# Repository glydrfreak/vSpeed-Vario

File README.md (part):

### This repository contains all previous prototypes. </br>
### Click <a href="https://github.com/glydrfreak/vSpeedVario-mini">here</a> for the final product repository. </br>
<table float="center">
  <tr>
    <td align="center" width=50%>
      <h1>v^Speed Vario</h1>
      Contents:</br>
      <a href="https://github.com/glydrfreak/vSpeedVario-mini">v^SPEED VARIO mini</a></br>
      <a href="#compare">Compare</a> </br>
      <a href="#vspeed-vario">Android App</a></br>
      <a href="#flyskyhy">iPhone App</a> </br>
      <a href="#solidworks">3D Printing</a> </br>
      <a href="#arduino-ide">Arduino Code</a> </br>
      <a href="#eagle-cad">Custom Circuit Board</a> </br>
      <a href="#bill-of-materials">Parts List</a> </br>
    </td>
    <td align="center"> 
      <h3>DIY Paragliding Variometer</h3>
       
      <h6>(Vertical Speed Indicator)</h6>
    </td>
  </tr>
</table>

<table>
  <tr>
    <td width=33% vAlign="top" align="center">
      <h2>v^SPEED VARIO mini</h2>
      <h3>$99</h3>
       </br>
         Email vSpeedVario@gmail.com to purchase </br>
      <a href="#vspeed-vario">Back to Top</a> </br>
    </td>
    <td width=66%> 
      <ul>
        <h3>SPECS:</h3>
        <li>Ultra-high precision barometric pressure sensor detects altitude changes as small as 10cm</li>
        <li>Lowest priced Bluetooth Variometer on the market</li>
        <li>iPhone users: Fully compatible with <a href="#flyskyhy">FlySkyHy</a> app</li>
        <li>Android users: <a href="#vspeed">v^SPEED</a> app new in Google Play Store</li>
        <li>Fully compatiple with Arduino IDE to easily change custom settings</li>
        <li>Mounts on risers with velcro</li>
        (leash, and velcro for both riser and vario included)
        <li>Tiny Size: 68x25x10mm (about the size of a man's thumb)</li>
        <li>3D printed cover screws onto circuit board </li>
          (black, white, yellow, or light blue)
        <li>Power switch, and volume buttons</li>
        <li>100mAh lipo battery with microUSB charging port</li>
        <li>7hr battery life while streaming bluetooth data</li>
        <li>1hr charging time</li>
        <li>Sale price: $99 each (subject to change)</li>
        <h3>OR -- DIY! --</h3><h6>(assuming you have a 3D printer, an SWD programmer, and a reflow oven)</h6>
        <li>1 hand assembled: ~ $70 each </li>
        <li>10 hand assembled: ~ $38 each</li>
        <li>10 machine assembled: ~ $89 each</li>
        <li>100 machine assembled: ~ $59 each</li>
      </ul>
    </td>
  </tr>
</table>

<table>
  <tr>
    <td width=33% vAlign="top" align="center">
      <h2>v^SPEED Vario</h2>
      
      <a href="#vspeed-vario">Back to Top</a> </br>
    </td>
    <td width="66%"> 
      <ul>
        <h3>Android App--</h3>
        I have modified Adafruit's "Bluefruit LE Connect" for Android and the source code can be found in the Android folder. Now published to Google Play! </br>
  </br>
        This app will give you a better image of what your v^SPEED Vario is doing as it transmits live bluetooth data of barometric altitude, vertical speed, and battery level. Other features include implemented GPS for GPS altitude, ground speed, and heading. The implemented Audio beeps are helpful for listening to each foot of climb as well as a variable sink tone. An implemented accelerometer is for keeping track of max G-force during a hard turn or spiral. The visual display includes a line chart of vertical speed, as well as scrolling altitude numbers so you can see your precise vertical velocity. The climb and sink thresholds are adjustable within the app, which also change the thresholds on the external vario automatically.
      </ul>
    </td>
  </tr>
</table>

<table>
  <tr>
    <td width=33% vAlign="top" align="center">
      <h2>Flyskyhy</h2>
      
      <a href="#vspeed-vario">Back to Top</a> </br>
    </td>
    <td width=66%> 
      <ul>
        <h3>iOS App by Renevision--</h3>
        I've been working with Rene to get v^SPEED VARIO compatible with the World's most popular Paragliding app! He's been very helpful throughout the process, and Flyskyhy is an unbeatable iPhone application when it comes to flying. v^Speed Vario is currently using the same protocol as SkyDrop variometers, so in the app when selecting your device, you must choose SkyDrop for the time being.  
      </ul>
    </td>
  </tr>
</table>

<h1>Prior Prototypes:</h1>

<table>
  <tr>
    <td width=33% vAlign="top" align="center">
      <h2>PROTOTYPE5</h2>
      <h4>(In Progress)</h4>
      
      <a href="#vspeed-vario">Back to Top</a> </br>
    </td>
    <td width=66%> 
      <ul>
        <h3>IMPROVEMENTS:</h3>
        <li>Nokia 5110 LCD is much cheaper</li>
        <li>2.9" e-Paper display was having interference issues</li>
        <li>Three buttons used for interfacing with menu</li>
        <li>Screw-together 3D printed case is much more printer friendly</li>
        <li>Size: 97x47x18mm</li>
        <li>Material cost for ten: ~ $54 each</li>
        <li>Material cost for one: ~ $96 each</li>
      </ul>
    </td>
  </tr>
</table>

<table>
  <tr>
    <td width=33% vAlign="top" align="center">
      <h2>PROTOTYPE4</h2>
      <h4>(Aborted)</h4>
      
      <a href="#vspeed-vario">Back to Top</a> </br>
    </td>
    <td width=66%> 
      <ul>
        <h3>IMPROVEMENTS:</h3>
        <li>Bluetooth compatible with:</li>
        <ul>
          <li>iPhone: Flyskyhy</li>
          <li>Android: v^Speed (soon to be published)</li>
        </ul>
        <li>2.9" e-Paper display is much larger</li>
        <li>Amplified electromagnetic buzzer is much louder</li>
        <li>Micro SD saves settings and any desired flight data</li>
        <li>Single Button power-on also used for interfacing with menu</li>
        <li>Machine assembly potential: All SMD components, except the switch</li>
        <li>Size: 100x40x30mm</li>
        <li>Material cost for ten: $69 each</li>
        <li>Material cost for one: $111 each</li>
      </ul>
    </td>
  </tr>
</table>

<table>
  <tr>
    <td width=33% align="center" vAlign="top">
      <h2>PROTOTYPE3</h2>
      <h4>(Fully Working)</h4>
       
      <a href="#vspeed-vario">Back to Top</a> </br>
    </td>
    <td width=66%> 
      <ul>
        <h3>IMPROVEMENTS:</h3>
        <li>Bluetooth compatible with:</li>
        <ul>
          <li>iPhone: Flyskyhy</li>
          <li>Android: v^SPEED (soon to be published)</li>
        </ul>
        <li>Adafruit Feather Bluefruit M0</li>
        <li>MS5611 Barometric Pressure/Temperature Sensor (SPI mode) </li>
        <li>Less than several INCHES of altitude noise with a simple averaging filter</li>
        <li>37 Altitude samples per second with the display screen ON</li>
        <li>56 Altitude samples per second while connected to your phone with the display screen OFF</li>
        <li>Size: 60x28x20mm (perfect for wrist watch, or riser mounting)</li>
        <li>0.66" OLED display (SPI mode)</li>
        <li>PS1740 Piezo Buzzer</li>
        <li>3D Printed Case</li>
        <li>Custom designed PCB</li>
        <li>Audio and a handful of widgets are implemented in each app</li>
        <li>Material cost for ten: $45 each</li>
        <li>Material cost for one: $77 each</li>
      </ul>
    </td>
  </tr>
</table>

<table>
  <tr>
    <td width=33% align="center" vAlign="top">
      <h2>PROTOTYPE2</h2>
      <h4>(Discontinued)</h4>
       
      <a href="#vspeed-vario">Back to Top</a> </br>
    </td>
    <td width=66%> 
      <ul>
        <h3>IMPROVEMENTS:</h3>
        <li>Bluetooth compatible with:</li>
        <ul>
          <li>iPhone: (Not yet compatible) </li>
          <li>Android: v^SPEED (soon to be published)</li>
        </ul>
        <li>Adafruit Feather Bluefruit 32u4</li>
        <li>MS5611 Barometric Pressure/Temperature Sensor (SPI mode) </li>
        <li>Less than several INCHES of altitude noise with a simple averaging filter</li>
        <li>21 Altitude samples per second with the display screen ON</li>
        <li>49 Altitude samples per second while connected to your phone with the display screen OFF</li>
        <li>Size: 60x20x28mm (perfect for wrist watch, or riser mounting)</li>
        <li>0.66" OLED display (SPI mode)</li>
        <li>PS1740 Piezo Buzzer</li>
        <li>3D Printed Case</li>
        <li>Custom designed PCB</li>
        <li>Audio and a handful of widgets are implemented in the  v^SPEED app</li>
        <li>Material cost for ten: $45 each</li>
        <li>Material cost for one: $77 each</li>
      </ul>
    </td>
  </tr>
</table>

<table>
  <tr>
    <td width=33% align="center" vAlign="top">
      <h2>PROTOTYPE1</h2>
      <h4>(One of a kind)</h4>
      
      <a href="#vspeed-vario">Back to Top</a> </br>
    </td>
    <td width=66%> 
      <ul>
        <h3>SPECIFICATIONS:</h3>
        <li>Arduino Nano</li>
        <li>BMP180 Barometric Pressure/Temperature Sensor (I2C mode)</li>
        <li>Just about a foot of altitude noise with a simple averaging filter</li>
        <li>13 Altitude samples per second</li>
        <li>Size: 60x20x28mm (perfect for wrist watch, or riser mounting)</li>
        <li>NOKIA5110 LCD Display (SPI mode)</li>
        <li>Backlight Control</li>
        <li>Volume Control</li>
        <li>PS1240 Piezo Buzzer</li>
        <li>Material cost for one: $20</li>
      </ul>
    </td>
  </tr>
</table>

<table border="1" align="center" >
  <tr> 
    <td VAlign="bottom"> 
      <h3>COMPARE:</h3><br/>
      <a href="#vspeed-vario">Back to Top</a> </br>
       
    </td>
    <td width="20%" align="center"> 	</td>
    <td width="20%" align="center"> 	</td>	
    <td width="20%" align="center"> 	</td>
    <td width="20%" align="center"> 	</td>
    <td width="20%" align="center"> 	</td>
    <td width="20%" align="center"> 	</td>
  </tr>
  <tr> 
    <td align="center"> <b>Model</b> </td>
    <td align="center"> <b>PROTOTYPE1</b>	</td>
    <td align="center"> <b>PROTOTYPE2</b>	</td>	
    <td align="center"> <b>PROTOTYPE3</b>	</td>
    <td align="center"> <b>PROTOTYPE4</b>	</td>
    <td align="center"> <b>PROTOTYPE5</b>	</td>
    <td align="center"> <b>PROTOTYPE6</b>	</td>
  </tr>
  <tr> 
    <td align="center"> <b>Height x Width x Thickness (mm)</b>	 </td>
    <td align="center"> 100 x 70 x 20		</td>
    <td align="center"> 	60 x 28 x 20	</td>	
    <td align="center">  60 x 28 x 20	</td>
    <td align="center"> 100 x 40 x 30	</td>
    <td align="center"> 97 x 47 x 18	</td>
    <td align="center"> 68 x 25 x 10	</td>
  </tr>
  <tr> 
    <td align="center"> <b>Controller</b>	 </td>
    <td align="center"> Arduino Nano		</td>
    <td align="center"> Bluefruit Feather 32u4	</td>	
    <td align="center"> Bluefruit Feather M0	</td>
    <td align="center"> Bluefruit Feather M0	</td>
    <td align="center"> Bluefruit Feather M0	</td>
    <td align="center"> ATSAMD21G18A-MU	</td>
  </tr>
  <tr> 
    <td align="center"> <b>Barometer</b>	 </td>
    <td align="center"> BMP180		</td>
    <td align="center"> MS5611	</td>	
    <td align="center"> MS5611	</td>
    <td align="center"> MS5611	</td>
    <td align="center"> MS5611	</td>
    <td align="center"> MS5611	</td>
  </tr>
  <tr> 
    <td align="center"> <b>Altitude Sample Rate (Hz)</b>	 </td>
    <td align="center"> 13		</td>
    <td align="center"> 21-49	</td>	
    <td align="center"> 37-56	</td>
    <td align="center"> (Not Tested Yet)	</td>
    <td align="center"> ~ 60 </td>
    <td align="center"> ~ 80 </td>
  </tr>  
  <tr> 
    <td align="center"> <b>Altitude Precision (cm)</b> </td>
    <td align="center"> 35		</td>
    <td align="center"> 11	</td>	
    <td align="center"> 10	</td>
    <td align="center"> (Not Tested Yet)	</td>
    <td align="center"> 10	</td>
    <td align="center"> ~ 8	</td>
  </tr>  
  <tr> 
    <td align="center"> <b>Android App Compatibility</b> </td>
    <td align="center"> -		</td>
    <td align="center"> v^SPEED	</td>	
    <td align="center"> v^SPEED	</td>
    <td align="center"> v^SPEED	</td>
    <td align="center"> v^SPEED	</td>
    <td align="center"> v^SPEED	</td>
  </tr> 
  <tr> 
    <td align="center"> <b>iPhone App Compatibility</b> </td>
    <td align="center"> - </td>
    <td align="center"> -	</td>	
    <td align="center"> Flyskyhy	</td>
    <td align="center"> Flyskyhy	</td>
    <td align="center"> Flyskyhy	</td>
    <td align="center"> Flyskyhy	</td>
  </tr> 
  <tr> 
    <td align="center"> <b>Battery</b> </td>
    <td align="center"> 9V </td>
    <td align="center"> BTG 150 mAh Li-Po 3.7V	</td>	
    <td align="center"> BTG 150 mAh Li-Po 3.7V	</td>
    <td align="center"> BTG 150 mAh Li-Po 3.7V	</td>
    <td align="center"> BTG 150 mAh Li-Po 3.7V	</td>
    <td align="center"> Adafruit 100 mAh Li-Po 3.7V	</td>
  </tr> 
  <tr> 
    <td align="center"> <b>Battery Life w/ Full Function</b> </td>
    <td align="center"> (Hasn't Died Yet) </td>
    <td align="center"> (Approx 8 hr)	</td>	
    <td align="center"> (Approx 8 hr)	</td>
    <td align="center"> (Not Tested Yet)	</td>
    <td align="center"> (Not Tested Yet)	</td>
    <td align="center"> (Not Tested Yet)	</td>
  </tr> 
  <tr> 
    <td align="center"> <b>Buzzer</b> </td>
    <td align="center"> PS1240 </td>
    <td align="center"> PS1740	</td>	
    <td align="center"> PS1740	</td>
    <td align="center"> BOT-03D-BUJEON	</td>
    <td align="center"> BOT-03D-BUJEON	</td>
    <td align="center"> SMT-1127-S-R	</td>
  </tr> 
  <tr> 
    <td align="center"> <b>Amplification</b> </td>
    <td align="center"> - </td>
    <td align="center"> - </td>	
    <td align="center"> -	</td>
    <td align="center"> Yes	</td>
    <td align="center"> Yes	</td>
    <td align="center"> Yes	</td>
  </tr> 
  <tr> 
    <td align="center"> <b>Volume Control</b> </td>
    <td align="center"> Thumbwheel </td>
    <td align="center"> Thumbwheel	</td>	
    <td align="center"> Thumbwheel	</td>
    <td align="center"> Digital	</td>
    <td align="center"> Digital	</td>
    <td align="center"> Digital	</td>
  </tr> 
  <tr> 
    <td align="center"> <b>Display</b> </td>
    <td align="center"> Nokia5110 LCD </td>
    <td align="center"> 0.66" OLED	</td>	
    <td align="center"> 0.66" OLED	</td>
    <td align="center"> 2.9" e-Paper	</td>
    <td align="center"> Nokia5110 LCD </td>
    <td align="center"> (Use Bluetooth) </td>
  </tr> 
  <tr> 
    <td align="center"> <b>Micro SD Slot</b> </td>
    <td align="center"> - </td>
    <td align="center"> -	</td>	
    <td align="center"> -	</td>
    <td align="center"> Yes	</td>
    <td align="center"> Yes	</td>
    <td align="center"> -	</td>
  </tr> 
  <tr> 
    <td align="center"> <b>User Control</b> </td>
    <td align="center"> Volume, Brightness, Power </td>
    <td align="center"> Volume, Power	</td>	
    <td align="center"> Volume, Power	</td>
    <td align="center"> Single Button	</td>
    <td align="center"> Three Button, Power	</td>
    <td align="center"> Two Button, Power	</td>
  </tr> 
  <tr> 
    <td align="center"> <b>Custom Settings</b> </td>
    <td align="center"> Arduino Upload </td>
    <td align="center"> Arduino Upload </td>	
    <td align="center"> Arduino Upload </td>
    <td align="center"> Settings Menu	</td>
    <td align="center"> Settings Menu	</td>
    <td align="center"> Arduino Upload </td>
  </tr> 
  <tr> 
    <td align="center"> <b>Mounting</b> </td>
    <td align="center"> Leg Strap </td>
    <td align="center"> Riser, Wrist	</td>	
    <td align="center"> Riser, Wrist	</td>
    <td align="center"> Riser	</td>
    <td align="center"> Leg Strap </td>
    <td align="center"> Leg Strap, Riser </td>
  </tr> 
  <tr> 
    <td align="center"> <b>Assembly</b> </td>
    <td align="center"> Cardboard, Protoboard, Wire </td>
    <td align="center"> Custom PCB Through-hole </td>    
    <td align="center"> Custom PCB Through-hole </td>
    <td align="center"> Custom PCB Surface Mount </td>  
    <td align="center"> Custom PCB Surface Mount </td>  
    <td align="center"> 100% machine assembly potential </td>  
  </tr> 
  <tr> 
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
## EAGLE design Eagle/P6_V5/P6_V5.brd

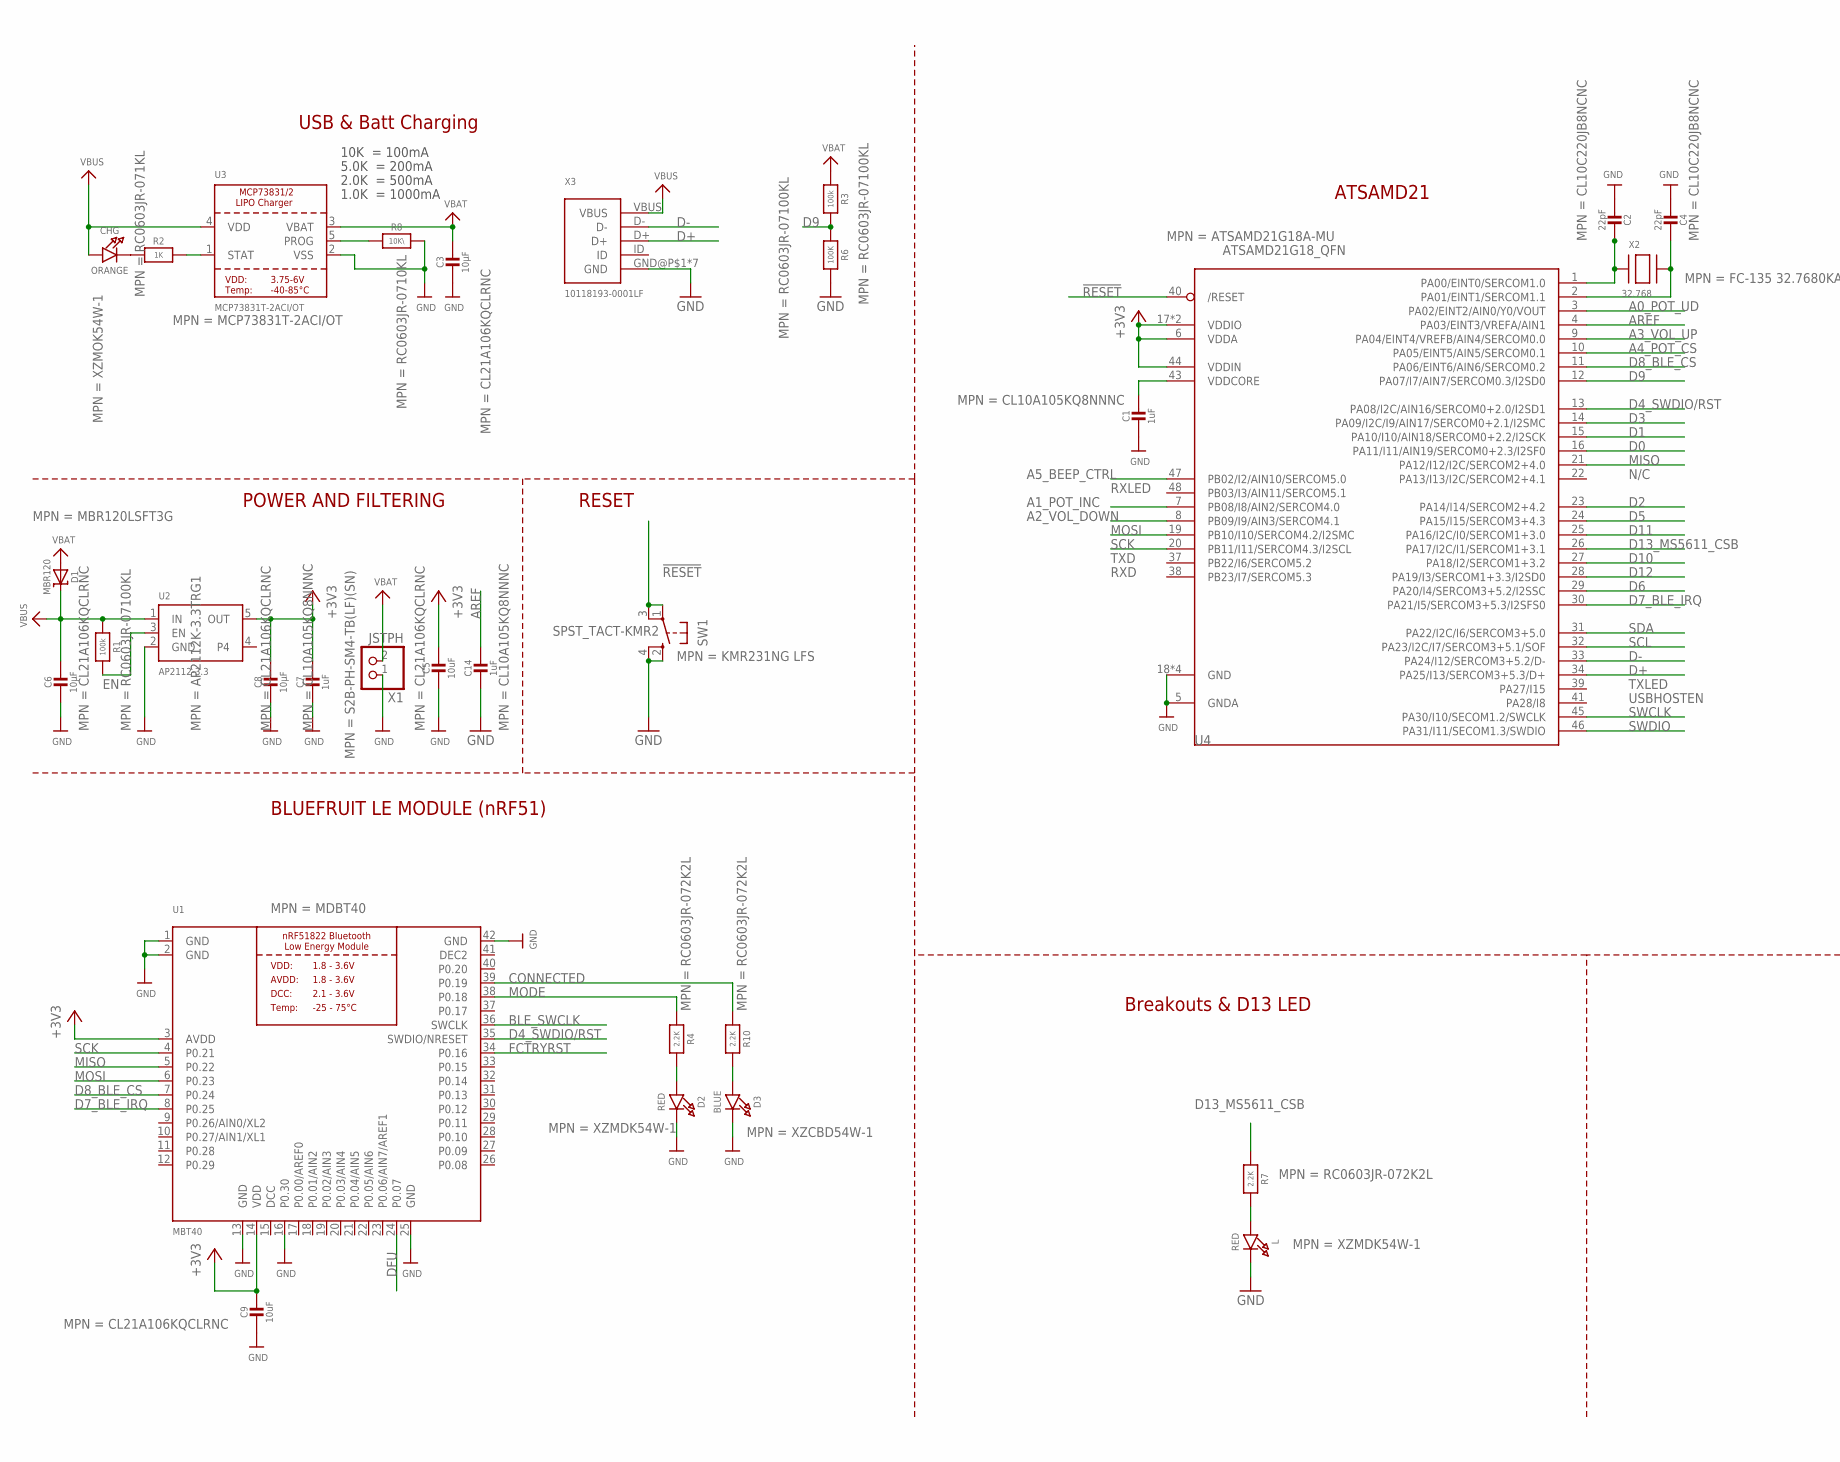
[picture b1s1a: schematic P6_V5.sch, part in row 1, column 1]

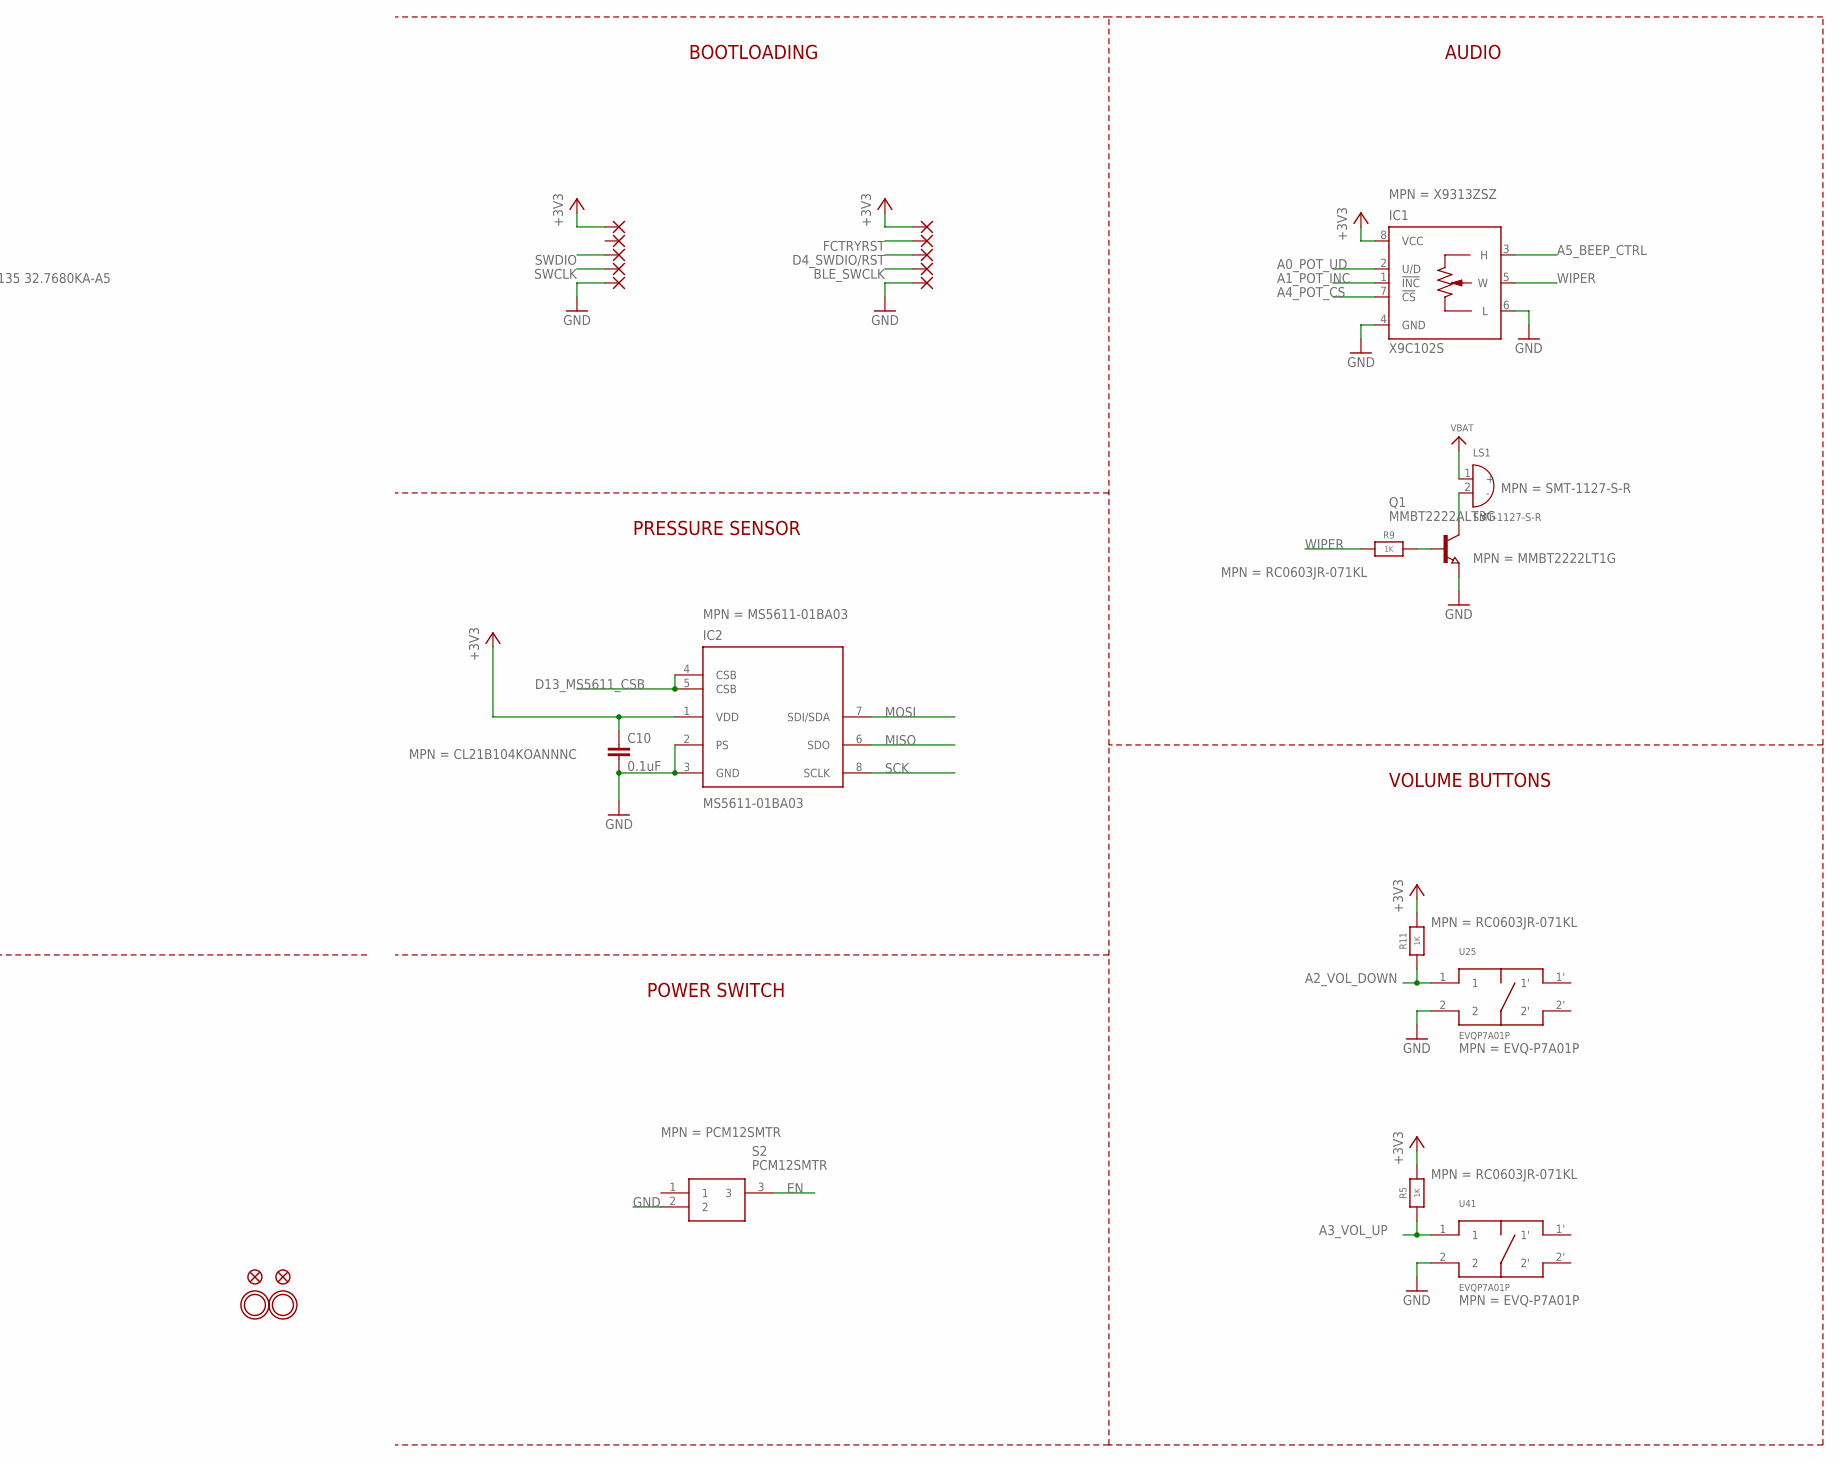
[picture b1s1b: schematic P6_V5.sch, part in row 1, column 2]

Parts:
C1, C7, C14: 1uF; 0603-NO; MPN CL10A105KQ8NNNC
C2, C4: 22pF; 0603-NO; MPN CL10C220JB8NCNC
C3, C6, C8: 10µF; 0805-NO; MPN CL21A106KQCLRNC
C5, C9: 10uF; 0805-NO; MPN CL21A106KQCLRNC
C10: 0.1uF; C0805K; MPN CL21B104KOANNNC
CHG: ORANGE; CHIPLED_0805_NOOUTLINE; MPN XZMOK54W-1
D1: MBR120; SOD-123; MPN MBR120LSFT3G
D2: RED; CHIPLED_0805_NOOUTLINE; MPN XZMDK54W-1
D3: BLUE; CHIPLED_0805_NOOUTLINE; MPN XZCBD54W-1
IC1: X9C102S; SOIC08; MPN X9313ZSZ
IC2: MS5611-01BA03; SON125P300X500X100-8N; MPN MS5611-01BA03
L: RED; CHIPLED_0805_NOOUTLINE; MPN XZMDK54W-1
LS1: SMT-1127-S-R; XDCR_SMT-1127-S-R; MPN SMT-1127-S-R
PAD1, PAD2, PAD3, PAD4, PAD5, PAD6, PAD7, PAD8, PAD9, PAD10: 1,6/0,8
Q1: MMBT2222ALT3G; SOT23; MPN MMBT2222LT1G
R1, R3: 100k; 0603-NO; MPN RC0603JR-07100KL
R2, R5, R9, R11: 1K; 0603-NO; MPN RC0603JR-071KL
R4, R7, R10: 2.2K; 0603-NO; MPN RC0603JR-072K2L
R6: 100K; 0603-NO; MPN RC0603JR-07100KL
R8: 10K\; 0603-NO; MPN RC0603JR-0710KL
S2: PCM12SMTR; PCM12SMTR_1; MPN PCM12SMTR
SW1: SPST_TACT-KMR2; KMR2; MPN KMR231NG LFS
U1: MBT40; BLE_MODULE_RAYTAC_MDBT40; MPN MDBT40
U2: AP2112-3.3; SOT23-5; MPN AP2112K-3.3TRG1
U3: MCP73831T-2ACI/OT; SOT23-5; MPN MCP73831T-2ACI/OT
U4: ATSAMD21G18_QFN; TQFN48_7MM; MPN ATSAMD21G18A-MU
U25, U41: EVQP7A01P; MPN EVQ-P7A01P
U$31, U$32: MOUNTINGHOLE2.5; MOUNTINGHOLE_2.5_PLATED
U$34, U$35: FIDUCIAL""; FIDUCIAL_1MM
X1: JSTPH; JSTPH2; MPN S2B-PH-SM4-TB(LF)(SN)
X2: 32.768; XTAL3215; MPN FC-135 32.7680KA-A5
X3: 10118193-0001LF

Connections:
!RESET: SW1.1, SW1.3 (P1), U4.40 (/RESET)
+3V3: C5.1, C7.1, C8.1, C9.1, C10.1, IC1.8 (VCC), IC2.1 (VDD), PAD2.1, PAD6.1, R5.2, R11.2, U1.3 (AVDD), U1.14 (VDD), U2.5 (OUT), U4.6 (VDDA), U4.17 (VDDIO), U4.36 (VDDIO), U4.44 (VDDIN)
A0_POT_UD: IC1.2 (U/D), U4.3 (PA02/EINT2/AIN0/Y0/VOUT)
A1_POT_INC: IC1.1 (!INC), U4.7 (PB08/I8/AIN2/SERCOM4.0)
A2_VOL_DOWN: R11.1, U4.8 (PB09/I9/AIN3/SERCOM4.1), U25.1
A3_VOL_UP: R5.1, U4.9 (PA04/EINT4/VREFB/AIN4/SERCOM0.0), U41.1
A4_POT_CS: IC1.7 (!CS), U4.10 (PA05/EINT5/AIN5/SERCOM0.1)
A5_BEEP_CTRL: IC1.3 (H), U4.47 (PB02/I2/AIN10/SERCOM5.0)
AREF: C14.1, U4.4 (PA03/EINT3/VREFA/AIN1)
BLE_SWCLK: PAD9.1, U1.36 (SWCLK)
CONNECTED: R10.1, U1.39 (P0.19)
D0: U4.16 (PA11/I11/AIN19/SERCOM0+2.3/I2SF0)
D1: U4.15 (PA10/I10/AIN18/SERCOM0+2.2/I2SCK)
D2: U4.23 (PA14/I14/SERCOM2+4.2)
D3: U4.14 (PA09/I2C/I9/AIN17/SERCOM0+2.1/I2SMC)
D4_SWDIO/RST: PAD8.1, U1.35 (SWDIO/NRESET), U4.13 (PA08/I2C/AIN16/SERCOM0+2.0/I2SD1)
D5: U4.24 (PA15/I15/SERCOM3+4.3)
D6: U4.29 (PA20/I4/SERCOM3+5.2/I2SSC)
D7_BLE_IRQ: U1.8 (P0.25), U4.30 (PA21/I5/SERCOM3+5.3/I2SFS0)
D8_BLE_CS: U1.7 (P0.24), U4.11 (PA06/EINT6/AIN6/SERCOM0.2)
D9: R3.2, R6.1, U4.12 (PA07/I7/AIN7/SERCOM0.3/I2SD0)
D10: U4.27 (PA18/I2/SERCOM1+3.2)
D11: U4.25 (PA16/I2C/I0/SERCOM1+3.0)
D12: U4.28 (PA19/I3/SERCOM1+3.3/I2SD0)
D13_MS5611_CSB: IC2.4 (CSB), IC2.5 (CSB), R7.1, U4.26 (PA17/I2C/I1/SERCOM1+3.1)
D+: U4.34 (PA25/I13/SERCOM3+5.3/D+), X3.D+
D-: U4.33 (PA24/I12/SERCOM3+5.2/D-), X3.D-
DCC: U1.15 (DCC)
DEC2: U1.41 (DEC2)
DFU: U1.24 (P0.07)
EN: R1.2, S2.3, U2.3 (EN)
FCTRYRST: PAD7.1, U1.34 (P0.16)
GND: C1.2, C2.2, C3.2, C4.2, C5.2, C6.2, C7.2, C8.2, C9.2, C10.2, C14.2, D2.C, D3.C, IC1.4 (GND), IC1.6 (L), IC2.2 (PS), IC2.3 (GND), L.C, PAD5.1, PAD10.1, Q1.2 (E), R6.2, R8.2, S2.2, SW1.2 (S), SW1.4 (S1), U1.1 (GND), U1.2 (GND), U1.13 (GND), U1.16 (P0.30), U1.25 (GND), U1.42 (GND), U2.2 (GND), U3.2 (VSS), U4.5 (GNDA), U4.18 (GND), U4.35 (GND), U4.42 (GND), U4.THERMAL (GND), U25.2, U41.2, X1.1, X3.GND@P$1 (GND), X3.GND@P$2 (GND), X3.GND@P$5 (GND), X3.GND@P$6 (GND), X3.GND@P$7 (GND), X3.GND@P$8 (GND), X3.GND@P$9 (GND)
MISO: IC2.6 (SDO), U1.5 (P0.22), U4.21 (PA12/I12/I2C/SERCOM2+4.0)
MODE: R4.1, U1.38 (P0.18)
MOSI: IC2.7 (SDI/SDA), U1.6 (P0.23), U4.19 (PB10/I10/SERCOM4.2/I2SMC)
unnamed: CHG.C, R2.1
unnamed: L.A, R7.2
unnamed: R2.2, U3.1 (STAT)
unnamed: R8.1, U3.5 (PROG)
unnamed: C2.1, U4.1 (PA00/EINT0/SERCOM1.0), X2.P$1
unnamed: D2.A, R4.2
unnamed: C4.1, U4.2 (PA01/EINT1/SERCOM1.1), X2.P$2
unnamed: D3.A, R10.2
unnamed: Q1.1 (B), R9.2
unnamed: LS1.2 (-), Q1.3 (C)
SCK: IC2.8 (SCLK), U1.4 (P0.21), U4.20 (PB11/I11/SERCOM4.3/I2SCL)
SCL: U4.32 (PA23/I2C/I7/SERCOM3+5.1/SOF)
SDA: U4.31 (PA22/I2C/I6/SERCOM3+5.0)
SWCLK: PAD4.1, U4.45 (PA30/I10/SECOM1.2/SWCLK)
SWDIO: PAD3.1, U4.46 (PA31/I11/SECOM1.3/SWDIO)
VBAT: C3.1, D1.A, LS1.1 (+), R3.1, U3.3 (VBAT), X1.2
VBUS: C6.1, CHG.A, D1.C, R1.1, U2.1 (IN), U3.4 (VDD), X3.VBUS
VDDCORE: C1.1, U4.43 (VDDCORE)
WIPER: IC1.5 (W), R9.1

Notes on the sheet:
POWER AND FILTERING
RESET
10K = 100mA
5.0K = 200mA
2.0K = 500mA
1.0K = 1000mA
N/C
TXLED
USBHOSTEN
RXLED
TXD
RXD
BLUEFRUIT LE MODULE (nRF51)
ATSAMD21
USB & Batt Charging
Breakouts & D13 LED
BOOTLOADING
PRESSURE SENSOR
AUDIO
POWER SWITCH
VOLUME BUTTONS

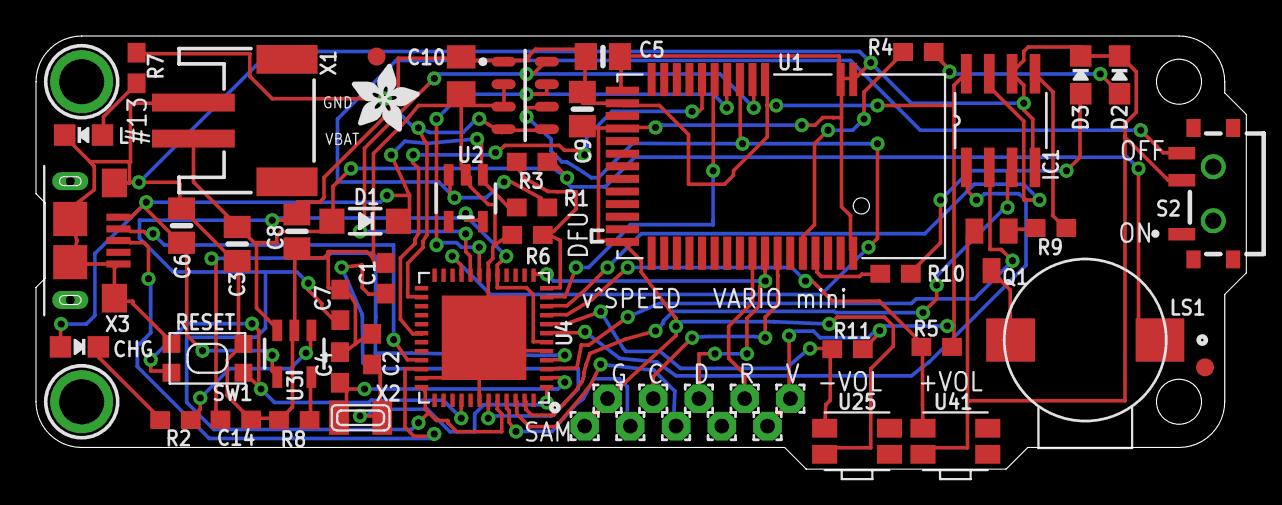
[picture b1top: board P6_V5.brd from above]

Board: 2 copper layers, 67.2 x 24.1 mm, 57 parts (0 on the bottom side), 41 nets.

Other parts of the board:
U$7: ADAFRUIT_3.5MM

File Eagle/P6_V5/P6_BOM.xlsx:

Parts | MPN | DESCRIPTION | DISTRIBUTER
C1, C7, C14 | CL10A105KQ8NNNC | CAP 1uF 0603 | DIGIKEY
C10 | CL21B104KOANNNC | CAP 0.1uF 0805 | DIGIKEY
C2, C4 | CL10C220JB8NCNC | CAP 22pF 0603 | DIGIKEY
C3, C5, C6, C8, C9 | CL21A106KQCLRNC | CAP 10uF 0805 | DIGIKEY
CHG | XZMOK54W-1 | LED ORANGE 0805 | DIGIKEY
D1 | MBR120LSFT3G | DIODE | DIGIKEY
D2, L | XZMDK54W-1 | LED RED 0805 | DIGIKEY
D3 | XZCBD54W-1 | LED BLUE 0805 | DIGIKEY
IC1 | X9313ZSZ | DIGIPOT 1K SOIC8 | DIGIKEY
IC2 | MS5611 | PRESSURE SENSOR | EBAY
LS1 | SMT-1127-S-R | SMT-1127-S-R | DIGIKEY
Q1 | MMBT2222LT1G | NPN SOT23 | DIGIKEY
R1, R3, R6 | RC0603JR-07100KL | RES 100K 0603 | DIGIKEY
R2, R5, R9, R11 | RC0603JR-071KL | RES 1K 0603 | DIGIKEY
R4, R7, R10 | RC0603JR-072K2L | RES 2.2K 0603 | DIGIKEY
R8 | RC0603JR-0710KL | RES 10K 0603 | DIGIKEY
S2 | PCM12SMTR | SLIDE SWITCH | DIGIKEY
SW1 | KMR231NG LFS | TACT SWITCH | DIGIKEY
U$4 | ATSAMD21G18A-MU | ATSAMD21G18_QFN | DIGIKEY
U1 | MDBT40 | NRF51822 BLE MODULE | EBAY
U2 | AP2112K-3.3TRG1 | VOLTAGE REGULATOR | DIGIKEY
U25, U41 | EVQ-P7A01P | TACT SWITCH RA | DIGIKEY
U3 | MCP73831T-2ACI/OT | LIPO CHARGER | DIGIKEY
X1 | S2B-PH-SM4-TB(LF)(SN) | JSTPH | DIGIKEY
X2 | FC-135 32.7680KA-A5 | CRYSTAL 32.768KHz | DIGIKEY
X3 | 10118193-0001LF | microUSB | DIGIKEY

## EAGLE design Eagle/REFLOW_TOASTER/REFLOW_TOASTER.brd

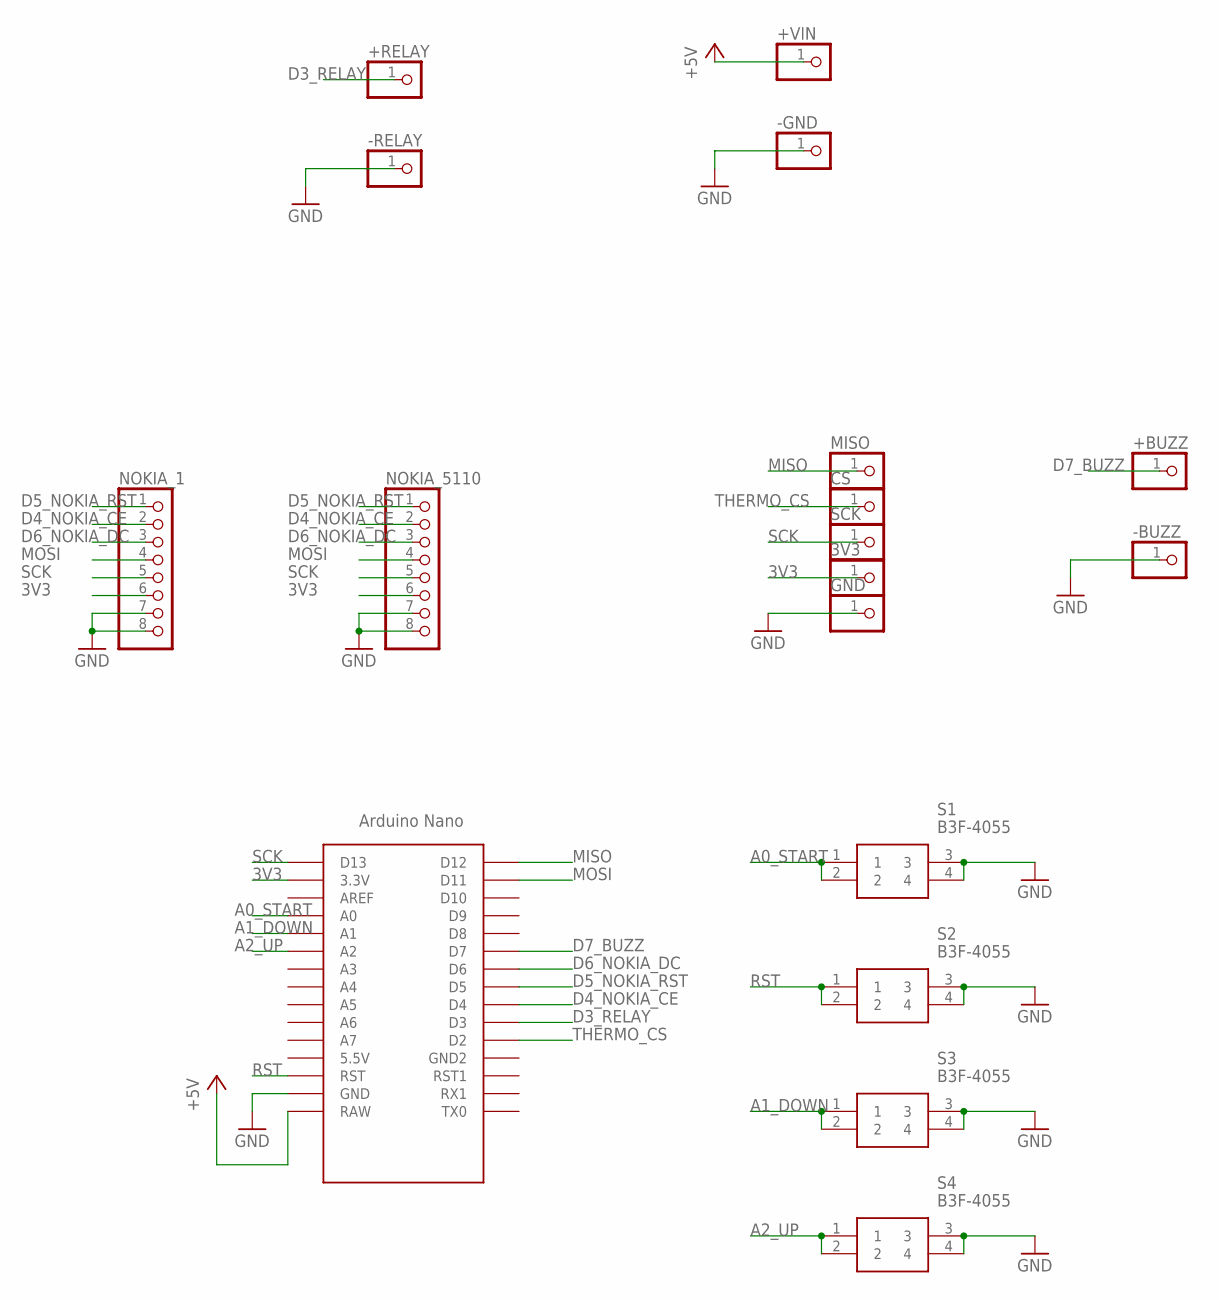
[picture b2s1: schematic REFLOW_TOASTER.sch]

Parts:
3V3: PINHD-1X1CB; 1X01-CLEANBIG
+BUZZ: PINHD-1X1CB; 1X01-CLEANBIG
+RELAY: PINHD-1X1CB; 1X01-CLEANBIG
+VIN: PINHD-1X1CB; 1X01-CLEANBIG
-BUZZ: PINHD-1X1CB; 1X01-CLEANBIG
-GND: PINHD-1X1CB; 1X01-CLEANBIG
-RELAY: PINHD-1X1CB; 1X01-CLEANBIG
CS: PINHD-1X1CB; 1X01-CLEANBIG
GND: PINHD-1X1CB; 1X01-CLEANBIG
MISO: PINHD-1X1CB; 1X01-CLEANBIG
NOKIA_1, NOKIA_5110: PINHD-1X8CLEANBIG; 1X08-CLEANBIG
S1, S2, S3, S4: B3F-4055
SCK: PINHD-1X1CB; 1X01-CLEANBIG
U$1: NANO

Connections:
3V3: 3V3.1, NOKIA_1.6, NOKIA_5110.6, U$1.3.3V
+5V: +VIN.1, U$1.RAW
A0_START: S1.1, S1.2, U$1.A0
A1_DOWN: S3.1, S3.2, U$1.A1
A2_UP: S4.1, S4.2, U$1.A2
D3_RELAY: +RELAY.1, U$1.D3
D4_NOKIA_CE: NOKIA_1.2, NOKIA_5110.2, U$1.D4
D5_NOKIA_RST: NOKIA_1.1, NOKIA_5110.1, U$1.D5
D6_NOKIA_DC: NOKIA_1.3, NOKIA_5110.3, U$1.D6
D7_BUZZ: +BUZZ.1, U$1.D7
GND: -BUZZ.1, -GND.1, -RELAY.1, GND.1, NOKIA_1.7, NOKIA_1.8, NOKIA_5110.7, NOKIA_5110.8, S1.3, S1.4, S2.3, S2.4, S3.3, S3.4, S4.3, S4.4, U$1.GND
MISO: MISO.1, U$1.D12
MOSI: NOKIA_1.4, NOKIA_5110.4, U$1.D11
RST: S2.1, S2.2, U$1.RST
SCK: NOKIA_1.5, NOKIA_5110.5, SCK.1, U$1.D13
THERMO_CS: CS.1, U$1.D2

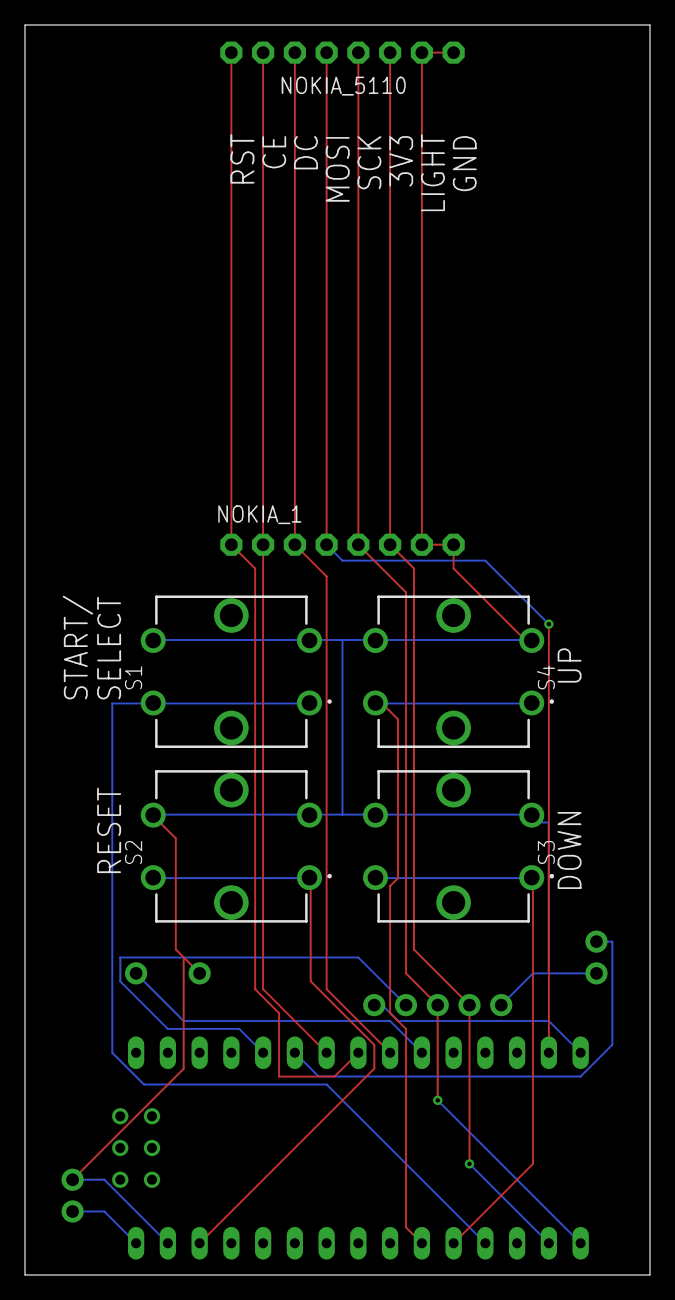
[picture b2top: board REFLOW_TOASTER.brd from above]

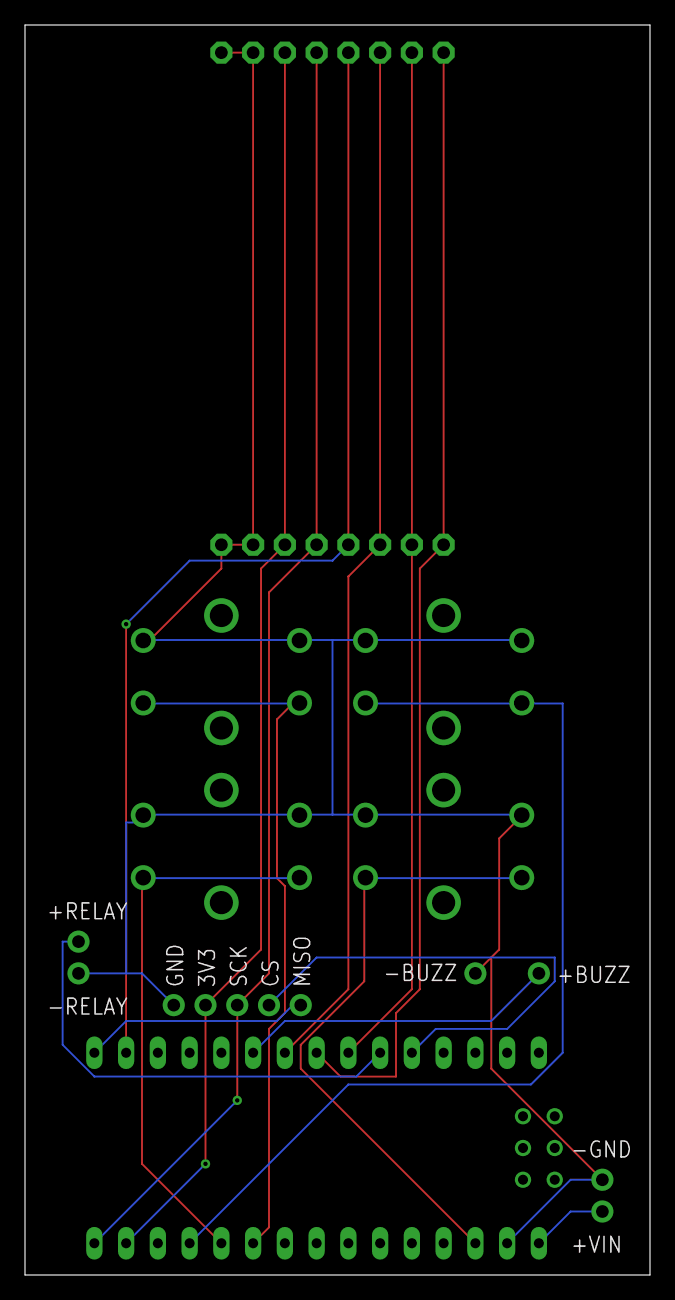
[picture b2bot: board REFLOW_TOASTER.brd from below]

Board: 2 copper layers, 50.0 x 100.0 mm, 18 parts (5 on the bottom side), 16 nets.

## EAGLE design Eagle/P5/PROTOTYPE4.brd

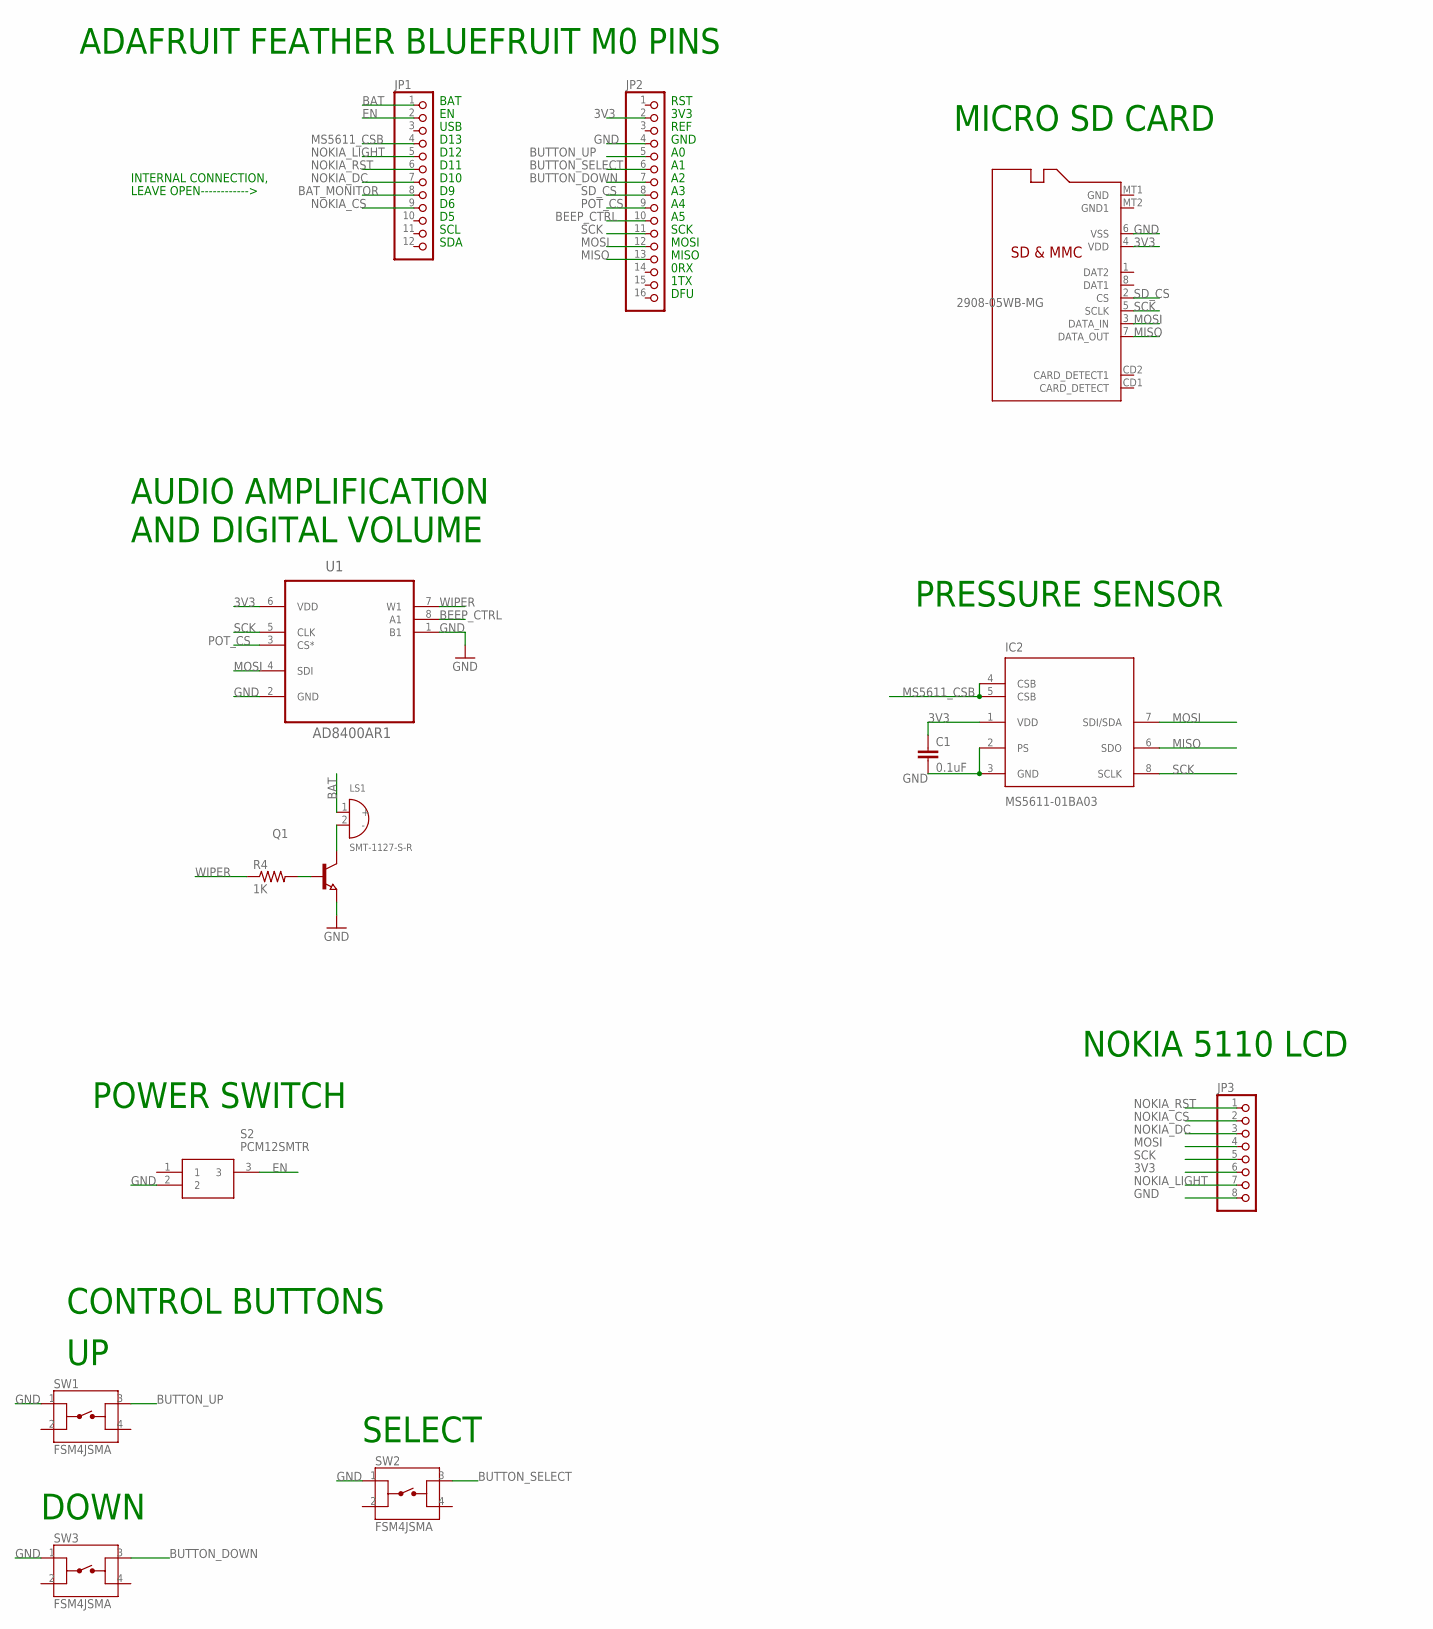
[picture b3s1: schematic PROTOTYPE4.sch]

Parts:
C1: 0.1uF; C0805K
IC2: MS5611-01BA03; SON125P300X500X100-8N
JP1: PINHD-1X12; 1X12
JP2: PINHD-1X16; 1X16
JP3: PINHD-1X8; 1X08
LS1: SMT-1127-S-R; XDCR_SMT-1127-S-R
Q1: NPN-TRANSISTOR_SOT23; SOT23
R4: 1K; R0805
S2: PCM12SMTR; PCM12SMTR_1
SW1, SW2, SW3: FSM4JSMA; TE_FSM4JSMA
U1: AD8400AR1; SOIC127P600X175-8N
U$1: 2908-05WB-MG; MICROSD

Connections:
3V3: C1.1, IC2.1 (VDD), JP2.2, JP3.6, U1.6 (VDD), U$1.4 (VDD)
BAT: JP1.1, LS1.1 (+)
BAT_MONITOR: JP1.8
BEEP_CTRL: JP2.10, U1.8 (A1)
BUTTON_DOWN: JP2.7, SW3.3
BUTTON_SELECT: JP2.6, SW2.3
BUTTON_UP: JP2.5, SW1.3
EN: JP1.2, S2.3
GND: C1.2, IC2.2 (PS), IC2.3 (GND), JP2.4, JP3.8, Q1.2 (E), S2.2, SW1.1, SW2.1, SW3.1, U1.1 (B1), U1.2 (GND), U$1.6 (VSS)
MISO: IC2.6 (SDO), JP2.13, U$1.7 (DATA_OUT)
MOSI: IC2.7 (SDI/SDA), JP2.12, JP3.4, U1.4 (SDI), U$1.3 (DATA_IN)
MS5611_CSB: IC2.4 (CSB), IC2.5 (CSB), JP1.4
unnamed: Q1.1 (B), R4.2
unnamed: LS1.2 (-), Q1.3 (C)
NOKIA_CS: JP1.9, JP3.2
NOKIA_DC: JP1.7, JP3.3
NOKIA_LIGHT: JP1.5, JP3.7
NOKIA_RST: JP1.6, JP3.1
POT_CS: JP2.9, U1.3 (CS*)
SCK: IC2.8 (SCLK), JP2.11, JP3.5, U1.5 (CLK), U$1.5 (SCLK)
SD_CS: JP2.8, U$1.2 (CS)
WIPER: R4.1, U1.7 (W1)

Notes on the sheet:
ADAFRUIT FEATHER BLUEFRUIT M0 PINS
DOWN
MICRO SD CARD
PRESSURE SENSOR
AUDIO AMPLIFICATION AND DIGITAL VOLUME
NOKIA 5110 LCD
LEAVE OPEN------------>
INTERNAL CONNECTION,
POWER SWITCH
SELECT
CONTROL BUTTONS
D10
D11
D12
D13
USB
BAT
SCL
SDA
RST
3V3
REF
GND
SCK
MOSI
MISO
0RX
1TX
DFU

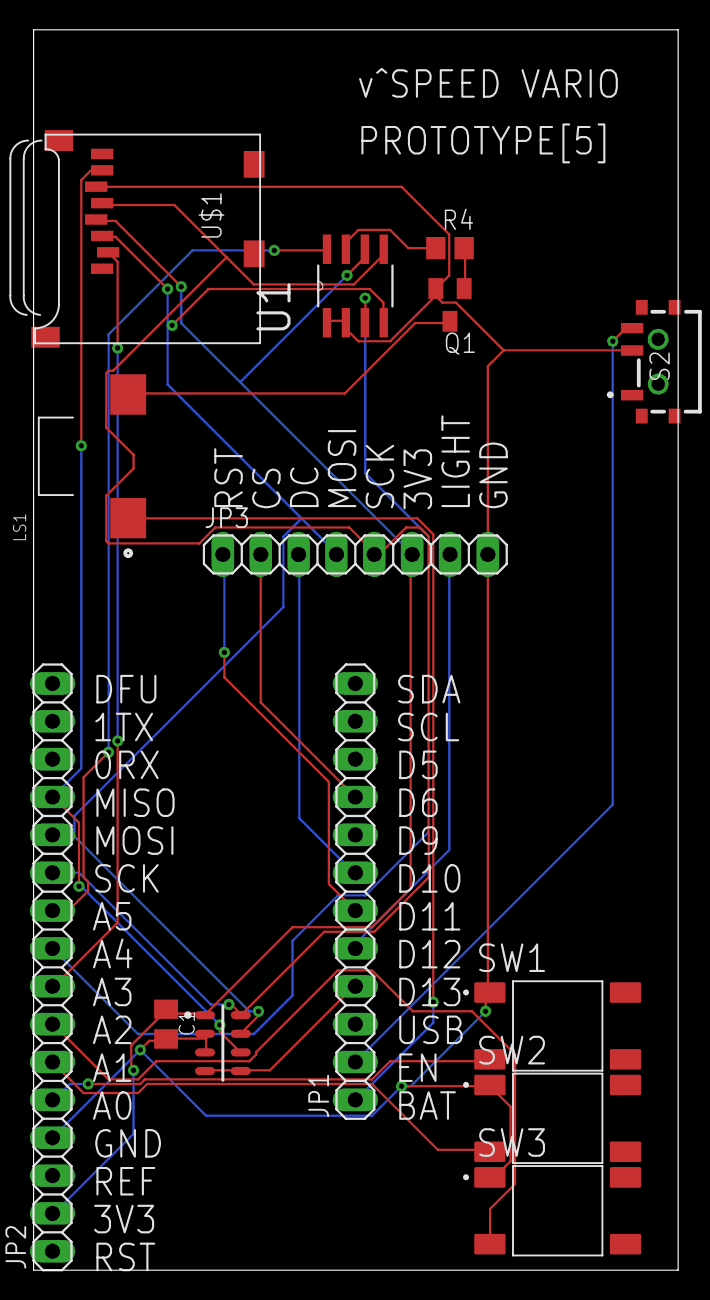
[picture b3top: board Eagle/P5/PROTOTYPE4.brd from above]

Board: 2 copper layers, 43.2 x 83.2 mm, 14 parts (0 on the bottom side), 21 nets.

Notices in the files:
parts and their libraries:
microbuilder: This work is placed in the public domain, and may be freely used for commercial and non-commercial work with the following conditions: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
